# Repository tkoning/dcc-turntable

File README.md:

# dcc-turntable
DCC control of a fleischmann turntable

Digital control of a fleischmann turntable can be achieved with an arduino nano

No modification of the original turntable is needed.
The turntable is controlled by four relays, 

DCC input is by means of the standard mynabay optocoupler circuit.
Manual Control is by means of a rotary encoder and an LCD display.

For indexing of the fleischmann turntable a power sensing circuit is used.
A seperate relais can be used to "flip" the polarity of the turntable brige.

code is annotated in dutch.

the turntable can be seen  in action on youtube.

https://www.youtube.com/watch?v=R1SMiSs2mZU

https://www.youtube.com/watch?v=gE1vPq5jKME

https://www.youtube.com/watch?v=S2jX1PM-Gi4

Schematic of the decoder is in the repository.

New software version 6 : position of bridge is retained at arduino shutdown by setting eeprom parameter in code

erratum : relay's must de mounted on the bottomside of the printed circuit board due to a design mistake regarding polarity of the relay coil.  Increase resitor r6 (dcc optocoupler circuit to 4,7 k)

I have noticed the fleischmann turntable electric engine to be unreliable. Especialy when cold the engine can cause short circuits
A new software version (vs10) cuts the power after a 3 second period
For this to work the positive power line has to be connected via the spare connecors of the aux1 relais

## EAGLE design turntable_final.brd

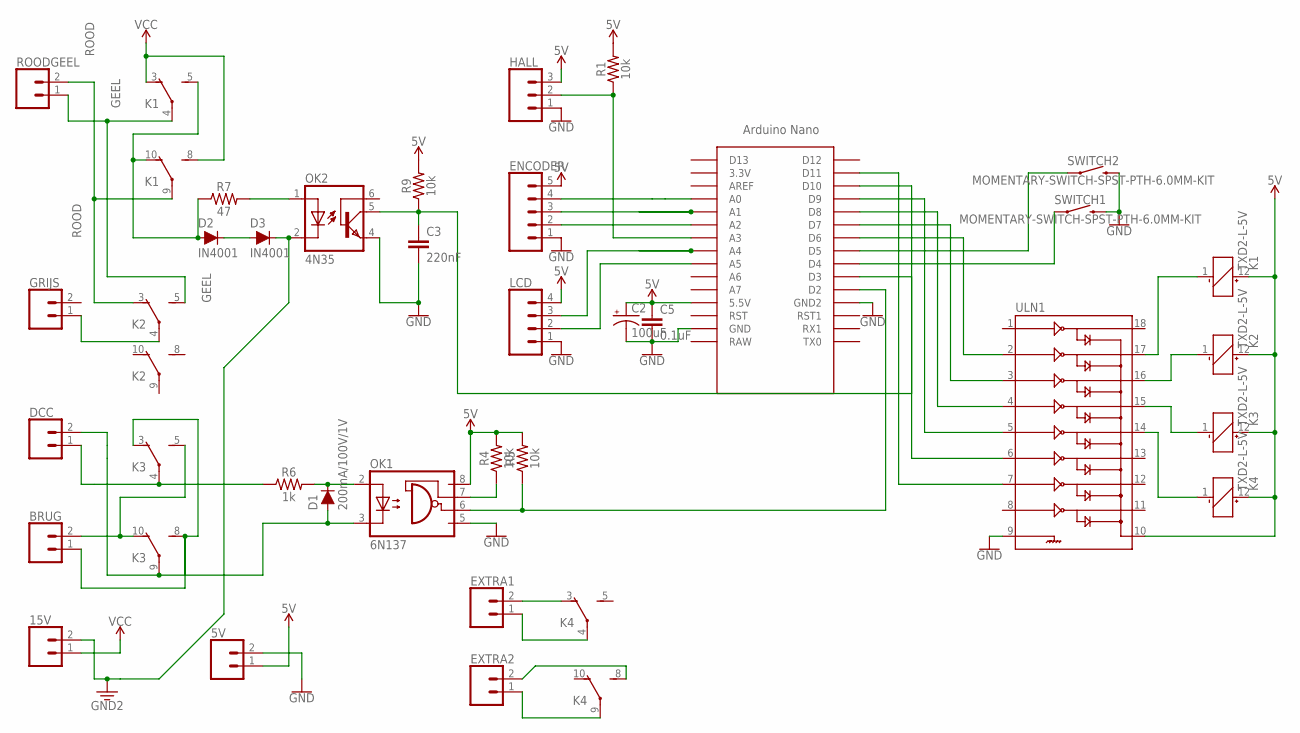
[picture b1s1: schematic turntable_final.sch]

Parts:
5V, 15V: CONN_023.5MM_LOCK; SCREWTERMINAL-3.5MM-2_LOCK
BRUG: CONN_023.5MM_LOCK; SCREWTERMINAL-3.5MM-2_LOCK
C2: 100uF; CPOL-RADIAL-2.5MM-5MM
C3: 220nF; CAP-PTH-SMALL-KIT
C5: 0.1uF; CAP-PTH-SMALL-KIT
D1: 200mA/100V/1V; DIODE-1N4148
D2, D3: IN4001; DIODE-1N4001
DCC: CONN_023.5MM_LOCK; SCREWTERMINAL-3.5MM-2_LOCK
ENCODER: CONN_05; 1X05
EXTRA1, EXTRA2: CONN_023.5MM_LOCK; SCREWTERMINAL-3.5MM-2_LOCK
GRIJS: CONN_023.5MM_LOCK; SCREWTERMINAL-3.5MM-2_LOCK
HALL: CONN_03; 1X03
K1, K2, K3, K4: TXD2-L-5V; TXD2
LCD: CONN_04; 1X04
OK1: 6N137; DIL08
OK2: 4N35; DIL06
R1, R4, R5, R9: 10k; AXIAL-0.3
R6: 1k; AXIAL-0.3
R7: 47; AXIAL-0.3
ROODGEEL: CONN_023.5MM_LOCK; SCREWTERMINAL-3.5MM-2_LOCK
SWITCH1, SWITCH2: MOMENTARY-SWITCH-SPST-PTH-6.0MM-KIT; TACTILE_SWITCH_PTH_6.0MM_KIT
U$1: NANO
ULN1: ULN2803DIP; DIL18

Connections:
5V: 5V.1, C2.1 (+), C5.1, ENCODER.5, HALL.3, K1.12 (+), K2.12 (+), K3.12 (+), K4.12 (+), LCD.4, OK1.8 (VCC), R1.P$2 (2), R4.P$2 (2), R5.P$2 (2), R9.P$2 (2), U$1.5V (5.5V), ULN1.10
GEEL: K1.4, K2.5 (S), ROODGEEL.1
GND: 5V.2, C2.2 (-), C3.2, C5.2, ENCODER.1, HALL.1, LCD.1, OK1.5 (GND), OK2.4 (EMI), SWITCH1.3 (2), SWITCH2.3 (2), U$1.GND, U$1.GND1 (GND2), ULN1.9
GND2: 15V.2, D3.C, OK2.2 (C)
unnamed: HALL.2, R1.P$1 (1), U$1.A3
unnamed: K3.1 (-), ULN1.15
unnamed: K1.1 (-), ULN1.17
unnamed: ENCODER.3, U$1.A1
unnamed: EXTRA2.1, K4.9
unnamed: K4.1 (-), ULN1.14
unnamed: OK1.7 (VE), R4.P$1 (1)
unnamed: DCC.1, K3.4, R6.P$1 (1)
unnamed: D1.A, DCC.2, K3.9, OK1.3 (C)
unnamed: ENCODER.4, U$1.A0
unnamed: K2.1 (-), ULN1.16
unnamed: OK1.6 (VO), R5.P$1 (1), U$1.D2
unnamed: D1.C, OK1.2 (A), R6.P$2 (2)
unnamed: ENCODER.2, U$1.A2
unnamed: BRUG.2, K3.5 (S), K3.10 (O)
unnamed: BRUG.1, K3.3 (O), K3.8 (S)
unnamed: D2.C, D3.A
unnamed: U$1.D10, ULN1.6
unnamed: OK2.1 (A), R7.P$2 (2)
unnamed: EXTRA1.2, K4.3 (O)
unnamed: C3.1, OK2.5 (COL), R9.P$1 (1), U$1.D3
unnamed: SWITCH1.1, U$1.D4
unnamed: SWITCH2.1, U$1.D5
unnamed: GRIJS.1, K2.4
unnamed: EXTRA1.1, K4.4
unnamed: D2.A, K1.5 (S), K1.10 (O), R7.P$1 (1)
unnamed: EXTRA2.2, K4.8 (S)
unnamed: U$1.D9, ULN1.5
unnamed: U$1.D8, ULN1.4
unnamed: U$1.D7, ULN1.3
unnamed: U$1.D6, ULN1.2
unnamed: LCD.3, U$1.A4
unnamed: LCD.2, U$1.A5
unnamed: U$1.D11, ULN1.7
ROOD: K1.9, K2.3 (O), ROODGEEL.2
VCC: 15V.1, K1.3 (O), K1.8 (S)

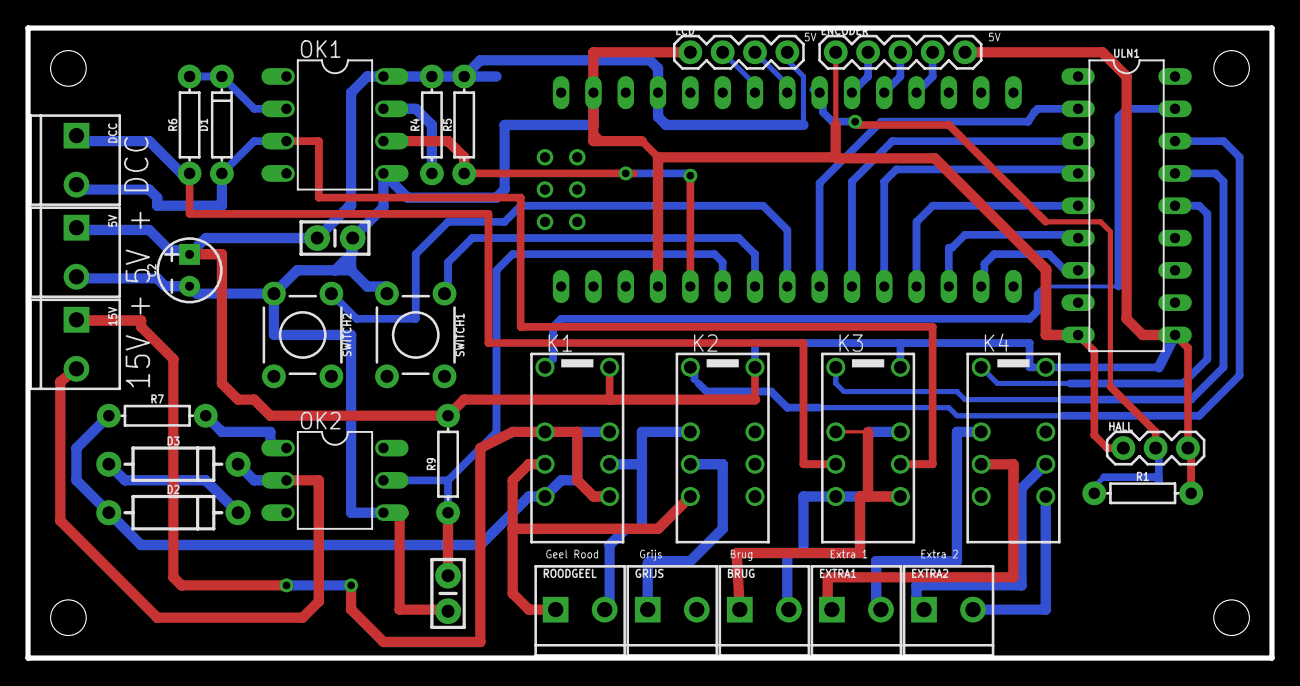
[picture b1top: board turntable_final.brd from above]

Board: 2 copper layers, 97.8 x 49.5 mm, 33 parts (0 on the bottom side), 40 nets.

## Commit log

2017-03-15 schematic turntable decoder
2017-03-15 Software adapted to new hardware setup
2017-03-16 prototype decoder
2017-03-16 Revised schematic turntable decoder
2017-03-28 Add files via upload
    Eagle files
2017-04-23 Add files via upload
    software version 6 optional use of eeprom storage
2017-04-24 EEPROM optie. Aux relais geativeerd, bugfixes
2017-08-10 Create DCC_draai_LCD_10
    with shortcircuit protection
2017-08-10 Add files via upload
    Includes additional software to protect against short circuits
2017-10-06 Add files via upload
    Experimental version
    Number of tracks can be edited by adjusting variable nsporen in code
2017-10-10 Add files via upload
    Revised version, bug fixes
2017-11-01 Add files via upload
    New version

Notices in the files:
parts and their libraries:
SparkFun-Connectors: Licensing: Creative Commons ShareAlike 4.0 International - https://creativecommons.org/licenses/by-sa/4.0
